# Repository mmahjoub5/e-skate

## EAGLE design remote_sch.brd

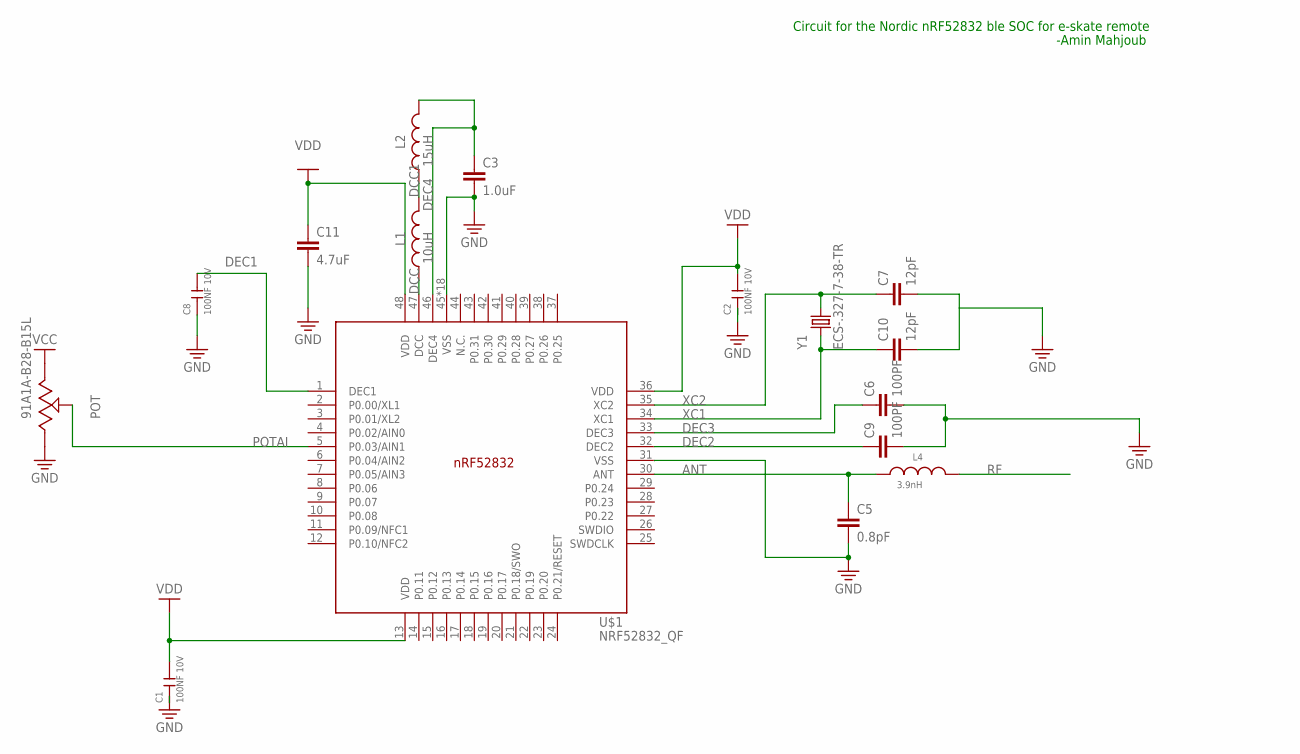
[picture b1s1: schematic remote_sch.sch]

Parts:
C1, C2, C8: 100NF 10V; C0402
C3: 1.0uF; 0402
C5: 0.8pF; 0402
C6, C9: 100PF; 0402
C7, C10: 12pF; 0603
C11: 4.7uF; 0402-TIGHT
L1: 10uH; WE-MAIA_2510
L2: 15uH; WE-MAIA_3015
L4: 3.9nH; WE-MK_0201
POT: 91A1A-B28-B15L; 91A1A-B28-B15L-ND
U$1: NRF52832_QF; QFN40P600X600X90-48_N
Y1: ECS-.327-7-38-TR

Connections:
ANT: C5.1, L4.1, U$1.30 (ANT)
DCC: L1.1, U$1.47 (DCC)
DCC1: L1.2, L2.1
DEC1: C8.2, U$1.1 (DEC1)
DEC2: C9.1, U$1.32 (DEC2)
DEC3: C6.1, U$1.33 (DEC3)
DEC4: C3.1, L2.2, U$1.46 (DEC4)
GND: C1.1, C2.1, C3.2, C5.2, C6.2, C7.2, C8.1, C9.2, C10.2, C11.2, POT.3, U$1.31 (VSS), U$1.45 (VSS), U$1.PAD (VSS), U$1.PAD@VIA01 (VSS), U$1.PAD@VIA02 (VSS), U$1.PAD@VIA03 (VSS), U$1.PAD@VIA04 (VSS), U$1.PAD@VIA05 (VSS), U$1.PAD@VIA06 (VSS), U$1.PAD@VIA07 (VSS), U$1.PAD@VIA08 (VSS), U$1.PAD@VIA09 (VSS), U$1.PAD@VIA10 (VSS), U$1.PAD@VIA11 (VSS), U$1.PAD@VIA12 (VSS), U$1.PAD@VIA13 (VSS), U$1.PAD@VIA14 (VSS), U$1.PAD@VIA15 (VSS), U$1.PAD@VIA16 (VSS)
POTAI: POT.2, U$1.5 (P0.03/AIN1)
RF: L4.2
VCC: POT.1
VDD: C1.2, C2.2, C11.1, U$1.13 (VDD), U$1.36 (VDD), U$1.48 (VDD)
XC1: C10.1, U$1.34 (XC1), Y1.1
XC2: C7.1, U$1.35 (XC2), Y1.4 (2)

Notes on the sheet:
Circuit for the Nordic nRF52832 ble SOC for e-skate remote
-Amin Mahjoub

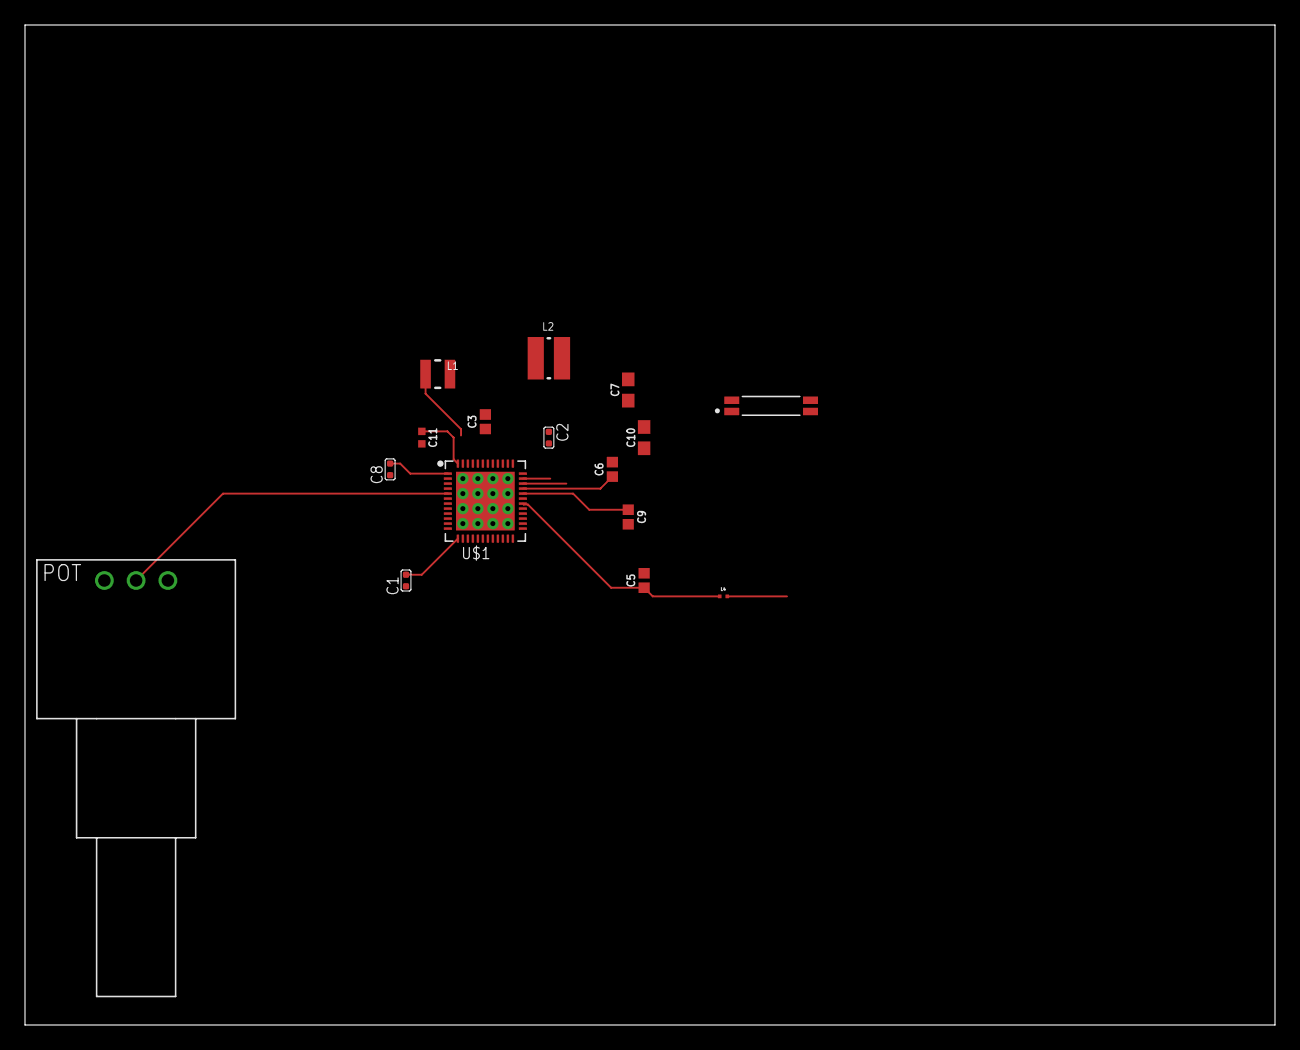
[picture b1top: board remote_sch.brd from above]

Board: 2 copper layers, 100.0 x 80.0 mm, 16 parts (0 on the bottom side), 12 nets.

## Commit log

2020-11-23 adding files
2020-11-23 started schematic
2020-11-26 circuit
2020-11-26 reomote circuit
2020-12-01 started routing need to add more layers to board
2020-12-01 stash issue
2020-12-11 created project
2020-12-18 Update e-skate_app

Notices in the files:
parts and their libraries:
SparkFun-Capacitors: Licensing: Creative Commons ShareAlike 4.0 International - https://creativecommons.org/licenses/by-sa/4.0
Wurth_Automotive_WE-MAIA: Copyright: Würth Elektronik
